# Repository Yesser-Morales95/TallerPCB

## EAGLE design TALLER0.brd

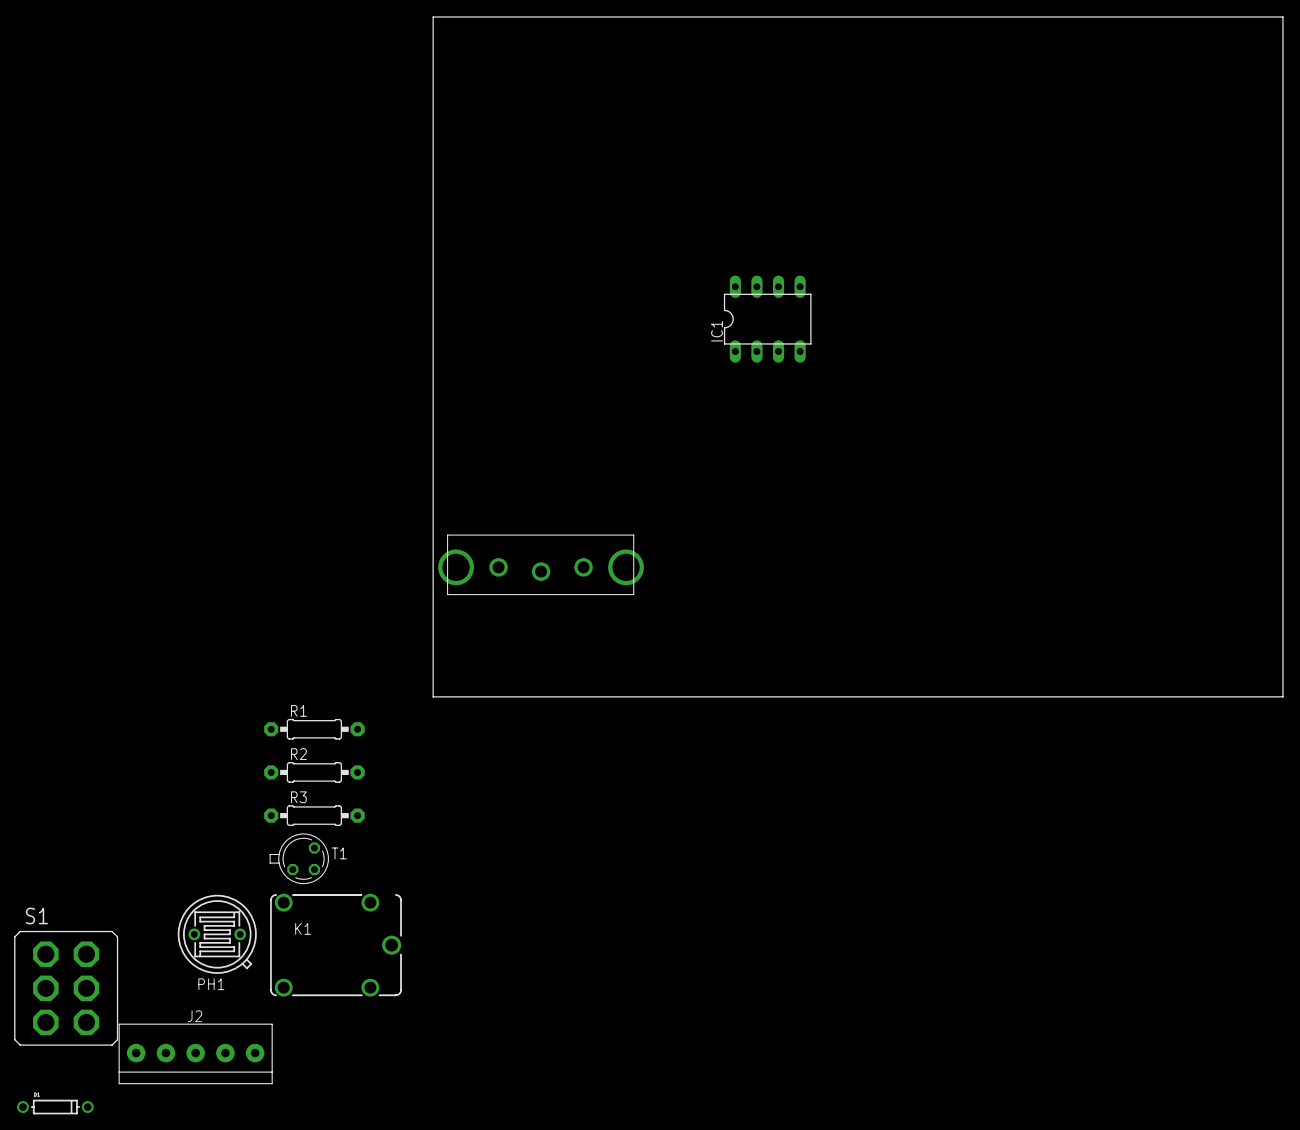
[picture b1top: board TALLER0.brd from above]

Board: 2 copper layers, 100.0 x 80.0 mm, 11 parts (0 on the bottom side), 9 nets, no tracks yet.

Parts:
D1: DO-1N4148
IC1: LM741P; DIL08
J2: 1X5; 1X05-3.5MM
K1: JJM1-12V; JJM1C
PH1: V1060_32; TO-5_V10
POT2: THUMBPOTV; THUMBWHEELV
R1, R2, R3: 0207/10
S1: 320-938
T1: 2N2222; TO18

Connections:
GNDA: IC1.4, J2.2, POT2.A, R1.1, R2.1, T1.1
unnamed: PH1.2, R1.2
unnamed: IC1.3, S1.1, S1.6
unnamed: IC1.2, S1.3, S1.4
unnamed: IC1.6, R3.2
unnamed: R2.2, R3.1, T1.2
unnamed: D1.A, K1.2, T1.3
unnamed: J2.5, K1.NO
V+: D1.C, IC1.7, J2.1, K1.1, PH1.1, POT2.E

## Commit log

2017-10-21 V1.0
2017-10-21 V1.01
2017-10-23 Final PCB
2017-10-23 Final PCB y simulacion
2019-06-04 RAS UNI 08/06/2019.
